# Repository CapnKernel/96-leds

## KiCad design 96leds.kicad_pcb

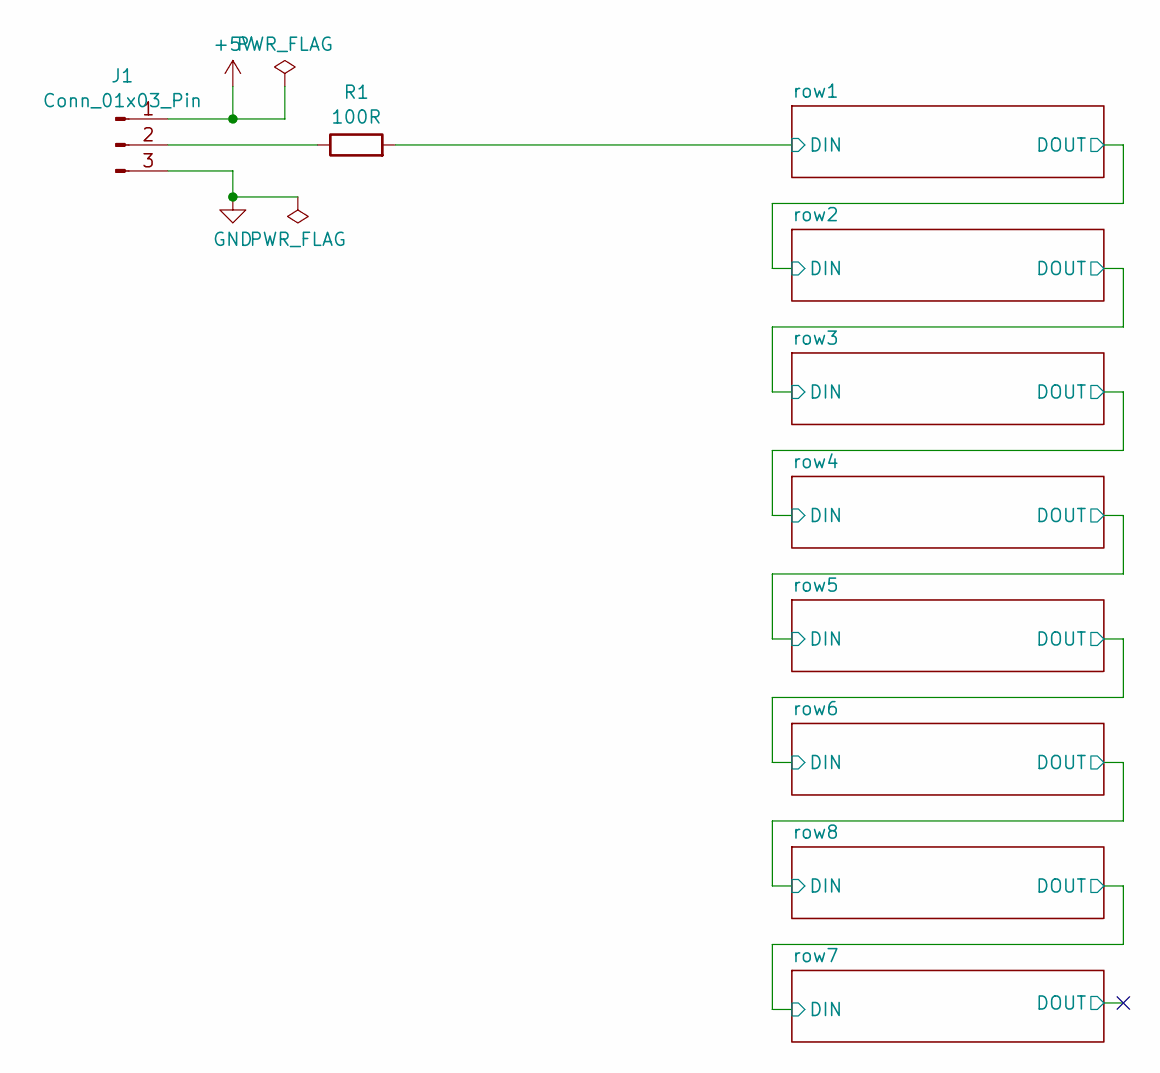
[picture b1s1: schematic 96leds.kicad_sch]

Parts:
J1: Conn_01x03_Pin; PinHeader_1x03_P2.54mm_Vertical
R1: 100R; R_0603_1608Metric

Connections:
+5V: J1.1; also elsewhere on the board
/row1/DIN: R1.2; also elsewhere on the board
GND: J1.3; also elsewhere on the board
unnamed: J1.2, R1.1

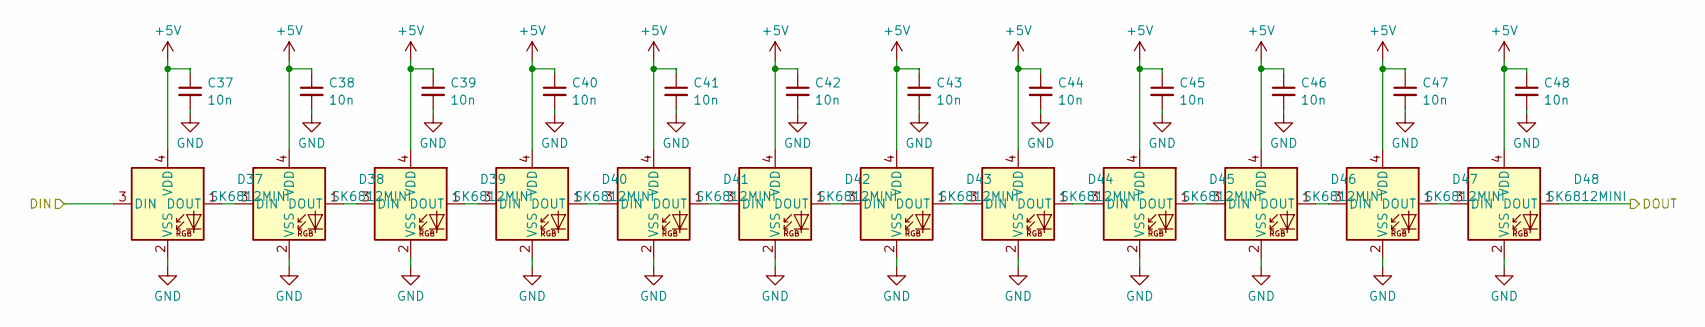
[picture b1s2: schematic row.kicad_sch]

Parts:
C37, C38, C39, C40, C41, C42, C43, C44, C45, C46, C47, C48: 10n; C_0603_1608Metric
D37, D38, D39, D40, D41, D42, D43, D44, D45, D46, D47, D48: SK6812MINI; LED_SK6812MINI_PLCC4_3.5x3.5mm_P1.75mm

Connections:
+5V: C37.1, C38.1, C39.1, C40.1, C41.1, C42.1, C43.1, C44.1, C45.1, C46.1, C47.1, C48.1, D37.4 (VDD), D38.4 (VDD), D39.4 (VDD), D40.4 (VDD), D41.4 (VDD), D42.4 (VDD), D43.4 (VDD), D44.4 (VDD), D45.4 (VDD), D46.4 (VDD), D47.4 (VDD), D48.4 (VDD); also elsewhere on the board
/row3/DOUT: D37.3 (DIN); also elsewhere on the board
/row4/DOUT: D48.1 (DOUT); also elsewhere on the board
GND: C37.2, C38.2, C39.2, C40.2, C41.2, C42.2, C43.2, C44.2, C45.2, C46.2, C47.2, C48.2, D37.2 (VSS), D38.2 (VSS), D39.2 (VSS), D40.2 (VSS), D41.2 (VSS), D42.2 (VSS), D43.2 (VSS), D44.2 (VSS), D45.2 (VSS), D46.2 (VSS), D47.2 (VSS), D48.2 (VSS); also elsewhere on the board
unnamed: D37.1 (DOUT), D38.3 (DIN)
unnamed: D38.1 (DOUT), D39.3 (DIN)
unnamed: D39.1 (DOUT), D40.3 (DIN)
unnamed: D40.1 (DOUT), D41.3 (DIN)
unnamed: D41.1 (DOUT), D42.3 (DIN)
unnamed: D42.1 (DOUT), D43.3 (DIN)
unnamed: D43.1 (DOUT), D44.3 (DIN)
unnamed: D44.1 (DOUT), D45.3 (DIN)
unnamed: D45.1 (DOUT), D46.3 (DIN)
unnamed: D46.1 (DOUT), D47.3 (DIN)
unnamed: D47.1 (DOUT), D48.3 (DIN)

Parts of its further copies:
C1, C2, C3, C4, C5, C6, C7, C8, C9, C10, C11, C12, C13, C14, C15, C16, C17, C18, C19, C20, C21, C22, C23, C24, C25, C26, C27, C28, C29, C30, C31, C32, C33, C34, C35, C36, C49, C50, C51, C52, C53, C54, C55, C56, C57, C58, C59, C60, C61, C62, C63, C64, C65, C66, C67, C68, C69, C70, C71, C72, C73, C74, C75, C76, C77, C78, C79, C80, C81, C82, C83, C84, C85, C86, C87, C88, C89, C90, C91, C92, C93, C94, C95, C96: 10n; C_0603_1608Metric
D1, D2, D3, D4, D5, D6, D7, D8, D9, D10, D11, D12, D13, D14, D15, D16, D17, D18, D19, D20, D21, D22, D23, D24, D25, D26, D27, D28, D29, D30, D31, D32, D33, D34, D35, D36, D49, D50, D51, D52, D53, D54, D55, D56, D57, D58, D59, D60, D61, D62, D63, D64, D65, D66, D67, D68, D69, D70, D71, D72, D73, D74, D75, D76, D77, D78, D79, D80, D81, D82, D83, D84, D85, D86, D87, D88, D89, D90, D91, D92, D93, D94, D95, D96: SK6812MINI; LED_SK6812MINI_PLCC4_3.5x3.5mm_P1.75mm

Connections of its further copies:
+5V: C1.1, C2.1, C3.1, C4.1, C5.1, C6.1, C7.1, C8.1, C9.1, C10.1, C11.1, C12.1, C13.1, C14.1, C15.1, C16.1, C17.1, C18.1, C19.1, C20.1, C21.1, C22.1, C23.1, C24.1, C25.1, C26.1, C27.1, C28.1, C29.1, C30.1, C31.1, C32.1, C33.1, C34.1, C35.1, C36.1, C49.1, C50.1, C51.1, C52.1, C53.1, C54.1, C55.1, C56.1, C57.1, C58.1, C59.1, C60.1, C61.1, C62.1, C63.1, C64.1, C65.1, C66.1, C67.1, C68.1, C69.1, C70.1, C71.1, C72.1, C73.1, C74.1, C75.1, C76.1, C77.1, C78.1, C79.1, C80.1, C81.1, C82.1, C83.1, C84.1, C85.1, C86.1, C87.1, C88.1, C89.1, C90.1, C91.1, C92.1, C93.1, C94.1, C95.1, C96.1, D1.4 (VDD), D2.4 (VDD), D3.4 (VDD), D4.4 (VDD), D5.4 (VDD), D6.4 (VDD), D7.4 (VDD), D8.4 (VDD), D9.4 (VDD), D10.4 (VDD), D11.4 (VDD), D12.4 (VDD), D13.4 (VDD), D14.4 (VDD), D15.4 (VDD), D16.4 (VDD), D17.4 (VDD), D18.4 (VDD), D19.4 (VDD), D20.4 (VDD), D21.4 (VDD), D22.4 (VDD), D23.4 (VDD), D24.4 (VDD), D25.4 (VDD), D26.4 (VDD), D27.4 (VDD), D28.4 (VDD), D29.4 (VDD), D30.4 (VDD), D31.4 (VDD), D32.4 (VDD), D33.4 (VDD), D34.4 (VDD), D35.4 (VDD), D36.4 (VDD), D49.4 (VDD), D50.4 (VDD), D51.4 (VDD), D52.4 (VDD), D53.4 (VDD), D54.4 (VDD), D55.4 (VDD), D56.4 (VDD), D57.4 (VDD), D58.4 (VDD), D59.4 (VDD), D60.4 (VDD), D61.4 (VDD), D62.4 (VDD), D63.4 (VDD), D64.4 (VDD), D65.4 (VDD), D66.4 (VDD), D67.4 (VDD), D68.4 (VDD), D69.4 (VDD), D70.4 (VDD), D71.4 (VDD), D72.4 (VDD), D73.4 (VDD), D74.4 (VDD), D75.4 (VDD), D76.4 (VDD), D77.4 (VDD), D78.4 (VDD), D79.4 (VDD), D80.4 (VDD), D81.4 (VDD), D82.4 (VDD), D83.4 (VDD), D84.4 (VDD), D85.4 (VDD), D86.4 (VDD), D87.4 (VDD), D88.4 (VDD), D89.4 (VDD), D90.4 (VDD), D91.4 (VDD), D92.4 (VDD), D93.4 (VDD), D94.4 (VDD), D95.4 (VDD), D96.4 (VDD); also elsewhere on the board
/row1/DIN: D1.3 (DIN); also elsewhere on the board
/row1/DOUT: D12.1 (DOUT), D13.3 (DIN)
/row2/DOUT: D24.1 (DOUT), D25.3 (DIN)
/row3/DOUT: D36.1 (DOUT); also elsewhere on the board
/row4/DOUT: D49.3 (DIN); also elsewhere on the board
/row5/DOUT: D60.1 (DOUT), D61.3 (DIN)
/row6/DOUT: D72.1 (DOUT), D73.3 (DIN)
/row7/DIN: D84.1 (DOUT), D85.3 (DIN)
/row7/DOUT: D96.1 (DOUT)
GND: C1.2, C2.2, C3.2, C4.2, C5.2, C6.2, C7.2, C8.2, C9.2, C10.2, C11.2, C12.2, C13.2, C14.2, C15.2, C16.2, C17.2, C18.2, C19.2, C20.2, C21.2, C22.2, C23.2, C24.2, C25.2, C26.2, C27.2, C28.2, C29.2, C30.2, C31.2, C32.2, C33.2, C34.2, C35.2, C36.2, C49.2, C50.2, C51.2, C52.2, C53.2, C54.2, C55.2, C56.2, C57.2, C58.2, C59.2, C60.2, C61.2, C62.2, C63.2, C64.2, C65.2, C66.2, C67.2, C68.2, C69.2, C70.2, C71.2, C72.2, C73.2, C74.2, C75.2, C76.2, C77.2, C78.2, C79.2, C80.2, C81.2, C82.2, C83.2, C84.2, C85.2, C86.2, C87.2, C88.2, C89.2, C90.2, C91.2, C92.2, C93.2, C94.2, C95.2, C96.2, D1.2 (VSS), D2.2 (VSS), D3.2 (VSS), D4.2 (VSS), D5.2 (VSS), D6.2 (VSS), D7.2 (VSS), D8.2 (VSS), D9.2 (VSS), D10.2 (VSS), D11.2 (VSS), D12.2 (VSS), D13.2 (VSS), D14.2 (VSS), D15.2 (VSS), D16.2 (VSS), D17.2 (VSS), D18.2 (VSS), D19.2 (VSS), D20.2 (VSS), D21.2 (VSS), D22.2 (VSS), D23.2 (VSS), D24.2 (VSS), D25.2 (VSS), D26.2 (VSS), D27.2 (VSS), D28.2 (VSS), D29.2 (VSS), D30.2 (VSS), D31.2 (VSS), D32.2 (VSS), D33.2 (VSS), D34.2 (VSS), D35.2 (VSS), D36.2 (VSS), D49.2 (VSS), D50.2 (VSS), D51.2 (VSS), D52.2 (VSS), D53.2 (VSS), D54.2 (VSS), D55.2 (VSS), D56.2 (VSS), D57.2 (VSS), D58.2 (VSS), D59.2 (VSS), D60.2 (VSS), D61.2 (VSS), D62.2 (VSS), D63.2 (VSS), D64.2 (VSS), D65.2 (VSS), D66.2 (VSS), D67.2 (VSS), D68.2 (VSS), D69.2 (VSS), D70.2 (VSS), D71.2 (VSS), D72.2 (VSS), D73.2 (VSS), D74.2 (VSS), D75.2 (VSS), D76.2 (VSS), D77.2 (VSS), D78.2 (VSS), D79.2 (VSS), D80.2 (VSS), D81.2 (VSS), D82.2 (VSS), D83.2 (VSS), D84.2 (VSS), D85.2 (VSS), D86.2 (VSS), D87.2 (VSS), D88.2 (VSS), D89.2 (VSS), D90.2 (VSS), D91.2 (VSS), D92.2 (VSS), D93.2 (VSS), D94.2 (VSS), D95.2 (VSS), D96.2 (VSS); also elsewhere on the board
unnamed: D1.1 (DOUT), D2.3 (DIN)
unnamed: D2.1 (DOUT), D3.3 (DIN)
unnamed: D3.1 (DOUT), D4.3 (DIN)
unnamed: D4.1 (DOUT), D5.3 (DIN)
unnamed: D5.1 (DOUT), D6.3 (DIN)
unnamed: D6.1 (DOUT), D7.3 (DIN)
unnamed: D7.1 (DOUT), D8.3 (DIN)
unnamed: D8.1 (DOUT), D9.3 (DIN)
unnamed: D9.1 (DOUT), D10.3 (DIN)
unnamed: D10.1 (DOUT), D11.3 (DIN)
unnamed: D11.1 (DOUT), D12.3 (DIN)
unnamed: D13.1 (DOUT), D14.3 (DIN)
unnamed: D14.1 (DOUT), D15.3 (DIN)
unnamed: D15.1 (DOUT), D16.3 (DIN)
unnamed: D16.1 (DOUT), D17.3 (DIN)
unnamed: D17.1 (DOUT), D18.3 (DIN)
unnamed: D18.1 (DOUT), D19.3 (DIN)
unnamed: D19.1 (DOUT), D20.3 (DIN)
unnamed: D20.1 (DOUT), D21.3 (DIN)
unnamed: D21.1 (DOUT), D22.3 (DIN)
unnamed: D22.1 (DOUT), D23.3 (DIN)
unnamed: D23.1 (DOUT), D24.3 (DIN)
unnamed: D25.1 (DOUT), D26.3 (DIN)
unnamed: D26.1 (DOUT), D27.3 (DIN)
unnamed: D27.1 (DOUT), D28.3 (DIN)
unnamed: D28.1 (DOUT), D29.3 (DIN)
unnamed: D29.1 (DOUT), D30.3 (DIN)
unnamed: D30.1 (DOUT), D31.3 (DIN)
unnamed: D31.1 (DOUT), D32.3 (DIN)
unnamed: D32.1 (DOUT), D33.3 (DIN)
unnamed: D33.1 (DOUT), D34.3 (DIN)
unnamed: D34.1 (DOUT), D35.3 (DIN)
unnamed: D35.1 (DOUT), D36.3 (DIN)
unnamed: D49.1 (DOUT), D50.3 (DIN)
unnamed: D50.1 (DOUT), D51.3 (DIN)
unnamed: D51.1 (DOUT), D52.3 (DIN)
unnamed: D52.1 (DOUT), D53.3 (DIN)
unnamed: D53.1 (DOUT), D54.3 (DIN)
unnamed: D54.1 (DOUT), D55.3 (DIN)
unnamed: D55.1 (DOUT), D56.3 (DIN)
unnamed: D56.1 (DOUT), D57.3 (DIN)
unnamed: D57.1 (DOUT), D58.3 (DIN)
unnamed: D58.1 (DOUT), D59.3 (DIN)
unnamed: D59.1 (DOUT), D60.3 (DIN)
unnamed: D61.1 (DOUT), D62.3 (DIN)
unnamed: D62.1 (DOUT), D63.3 (DIN)
unnamed: D63.1 (DOUT), D64.3 (DIN)
unnamed: D64.1 (DOUT), D65.3 (DIN)
unnamed: D65.1 (DOUT), D66.3 (DIN)
unnamed: D66.1 (DOUT), D67.3 (DIN)
unnamed: D67.1 (DOUT), D68.3 (DIN)
unnamed: D68.1 (DOUT), D69.3 (DIN)
unnamed: D69.1 (DOUT), D70.3 (DIN)
unnamed: D70.1 (DOUT), D71.3 (DIN)
unnamed: D71.1 (DOUT), D72.3 (DIN)
unnamed: D73.1 (DOUT), D74.3 (DIN)
unnamed: D74.1 (DOUT), D75.3 (DIN)
unnamed: D75.1 (DOUT), D76.3 (DIN)
unnamed: D76.1 (DOUT), D77.3 (DIN)
unnamed: D77.1 (DOUT), D78.3 (DIN)
unnamed: D78.1 (DOUT), D79.3 (DIN)
unnamed: D79.1 (DOUT), D80.3 (DIN)
unnamed: D80.1 (DOUT), D81.3 (DIN)
unnamed: D81.1 (DOUT), D82.3 (DIN)
unnamed: D82.1 (DOUT), D83.3 (DIN)
unnamed: D83.1 (DOUT), D84.3 (DIN)
unnamed: D85.1 (DOUT), D86.3 (DIN)
unnamed: D86.1 (DOUT), D87.3 (DIN)
unnamed: D87.1 (DOUT), D88.3 (DIN)
unnamed: D88.1 (DOUT), D89.3 (DIN)
unnamed: D89.1 (DOUT), D90.3 (DIN)
unnamed: D90.1 (DOUT), D91.3 (DIN)
unnamed: D91.1 (DOUT), D92.3 (DIN)
unnamed: D92.1 (DOUT), D93.3 (DIN)
unnamed: D93.1 (DOUT), D94.3 (DIN)
unnamed: D94.1 (DOUT), D95.3 (DIN)
unnamed: D95.1 (DOUT), D96.3 (DIN)

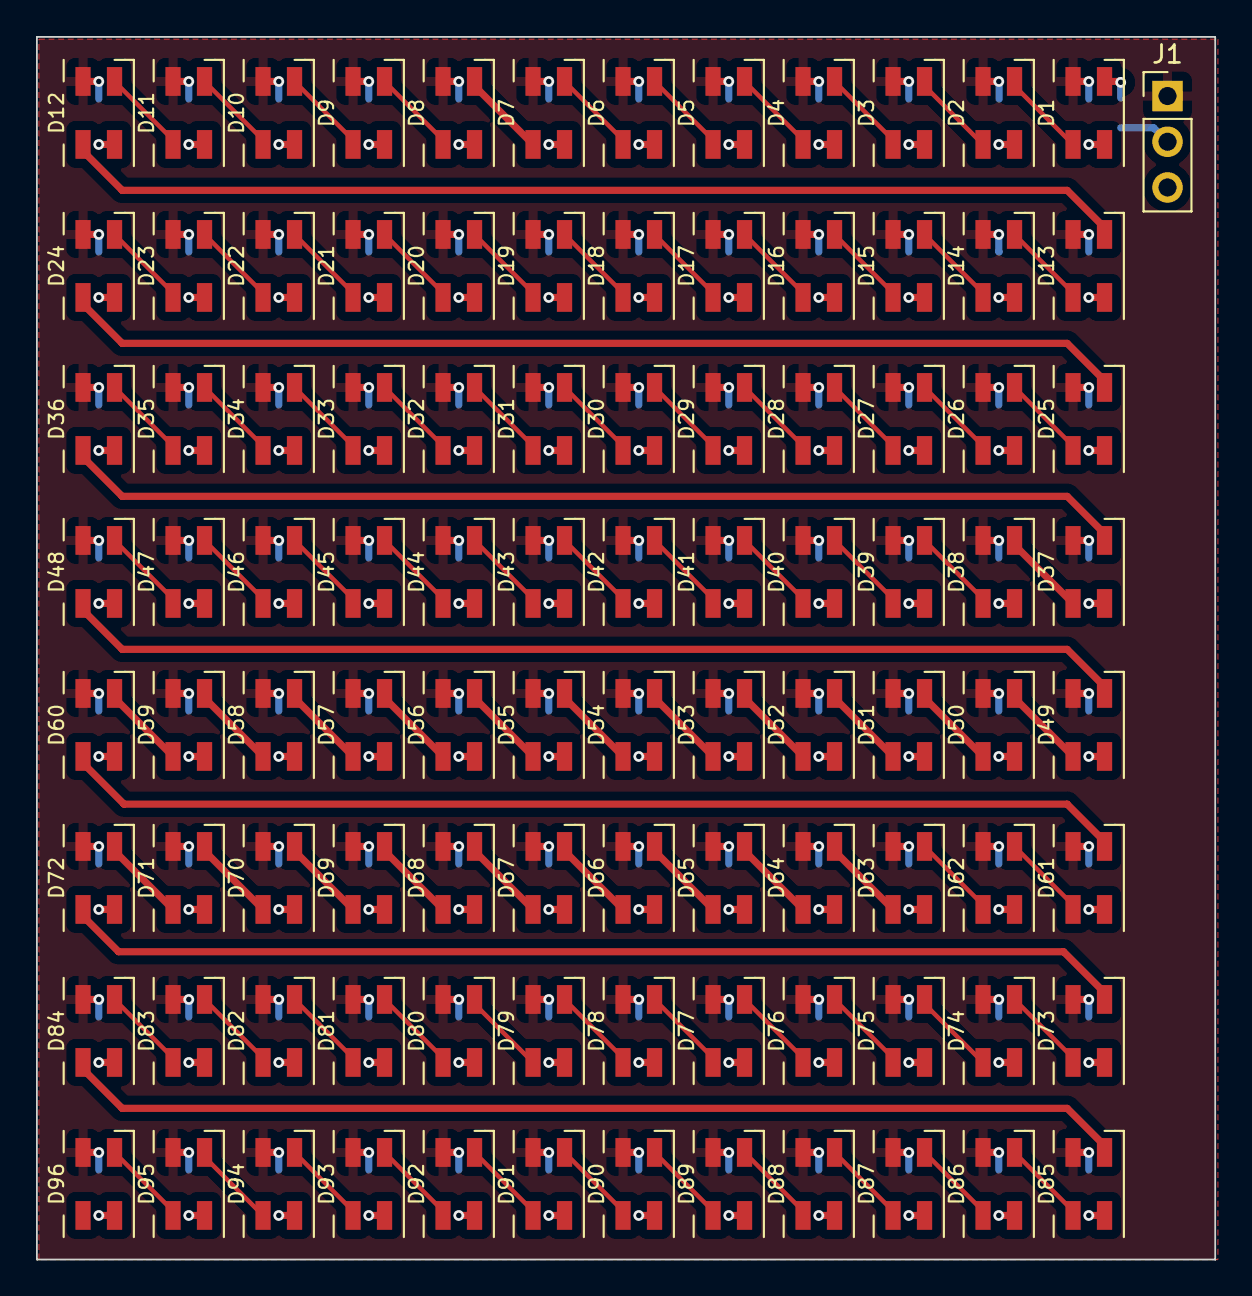
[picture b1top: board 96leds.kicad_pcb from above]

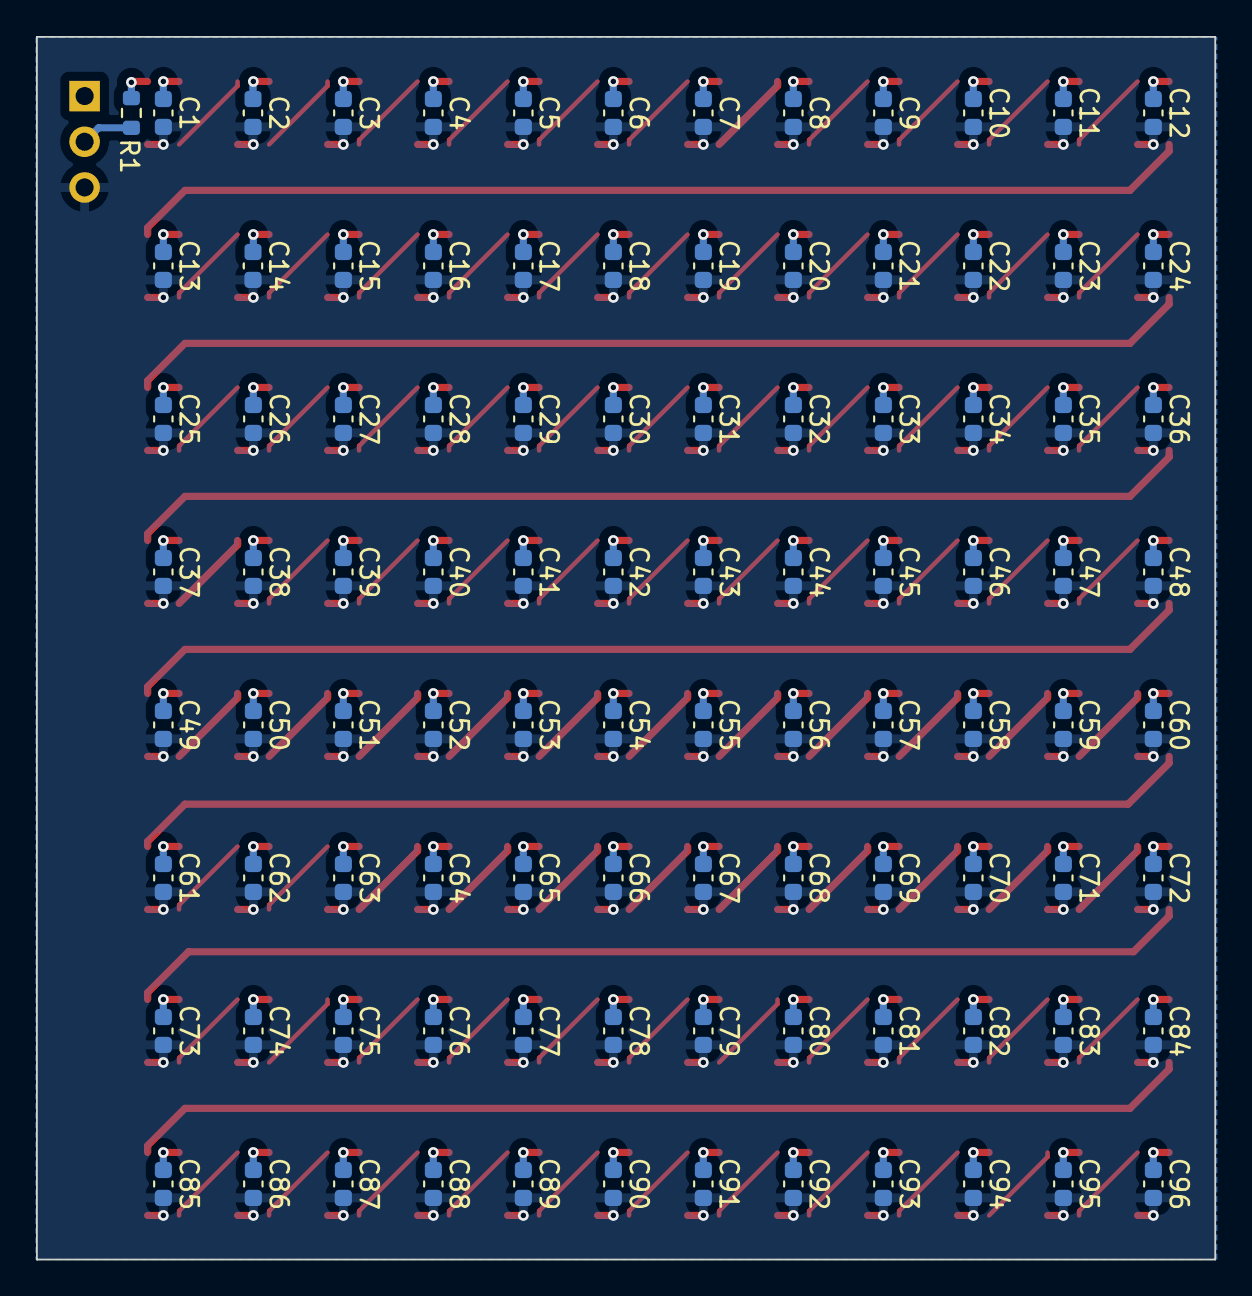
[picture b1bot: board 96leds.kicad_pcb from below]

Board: 2 copper layers, 65.5 x 67.9 mm, 194 parts (97 on the bottom side), 99 nets.

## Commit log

2024-02-10 First commit.
